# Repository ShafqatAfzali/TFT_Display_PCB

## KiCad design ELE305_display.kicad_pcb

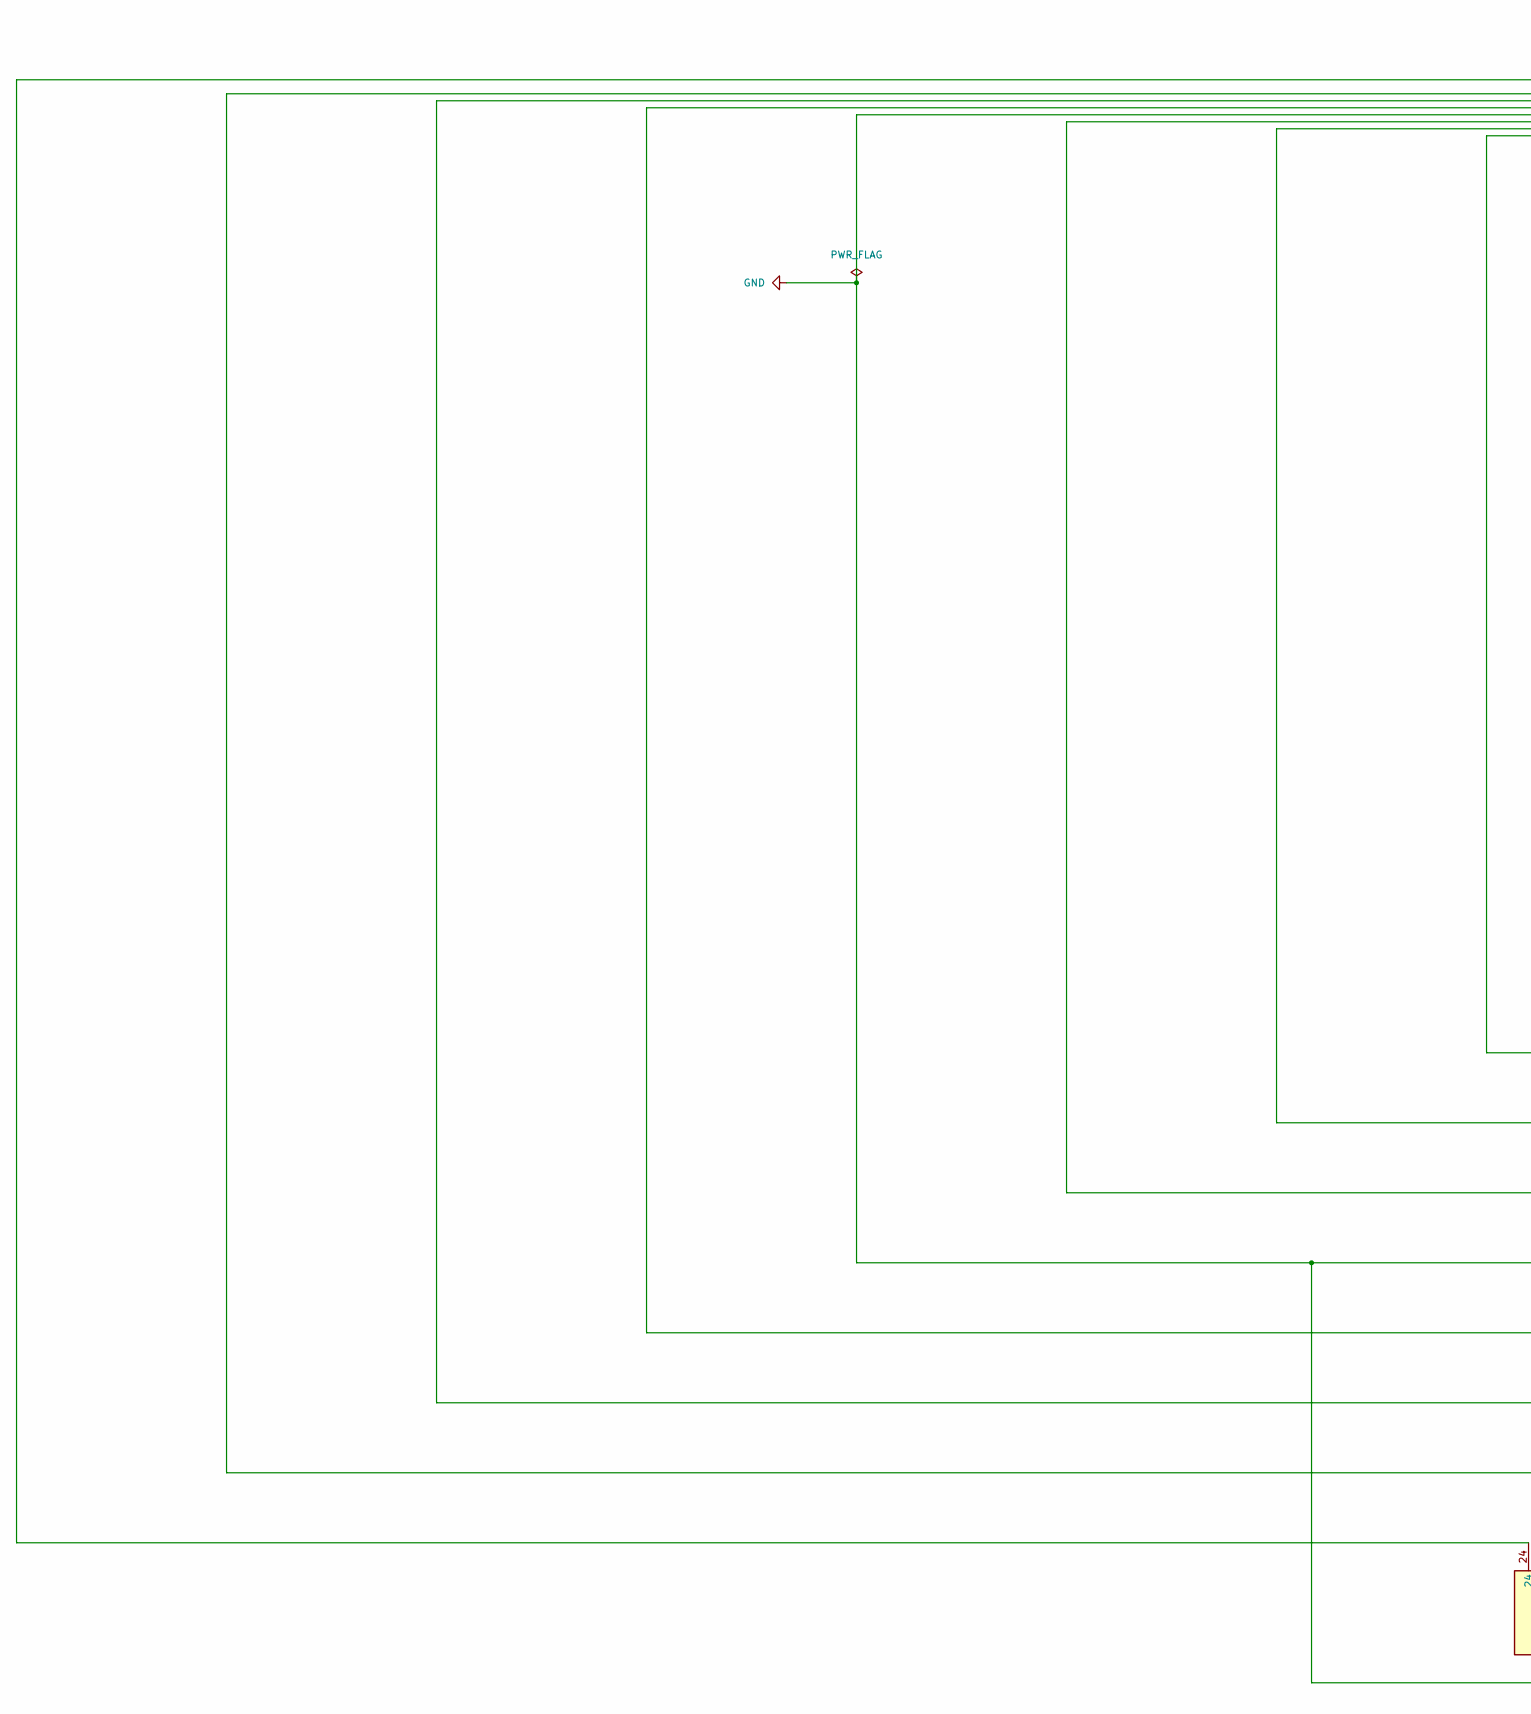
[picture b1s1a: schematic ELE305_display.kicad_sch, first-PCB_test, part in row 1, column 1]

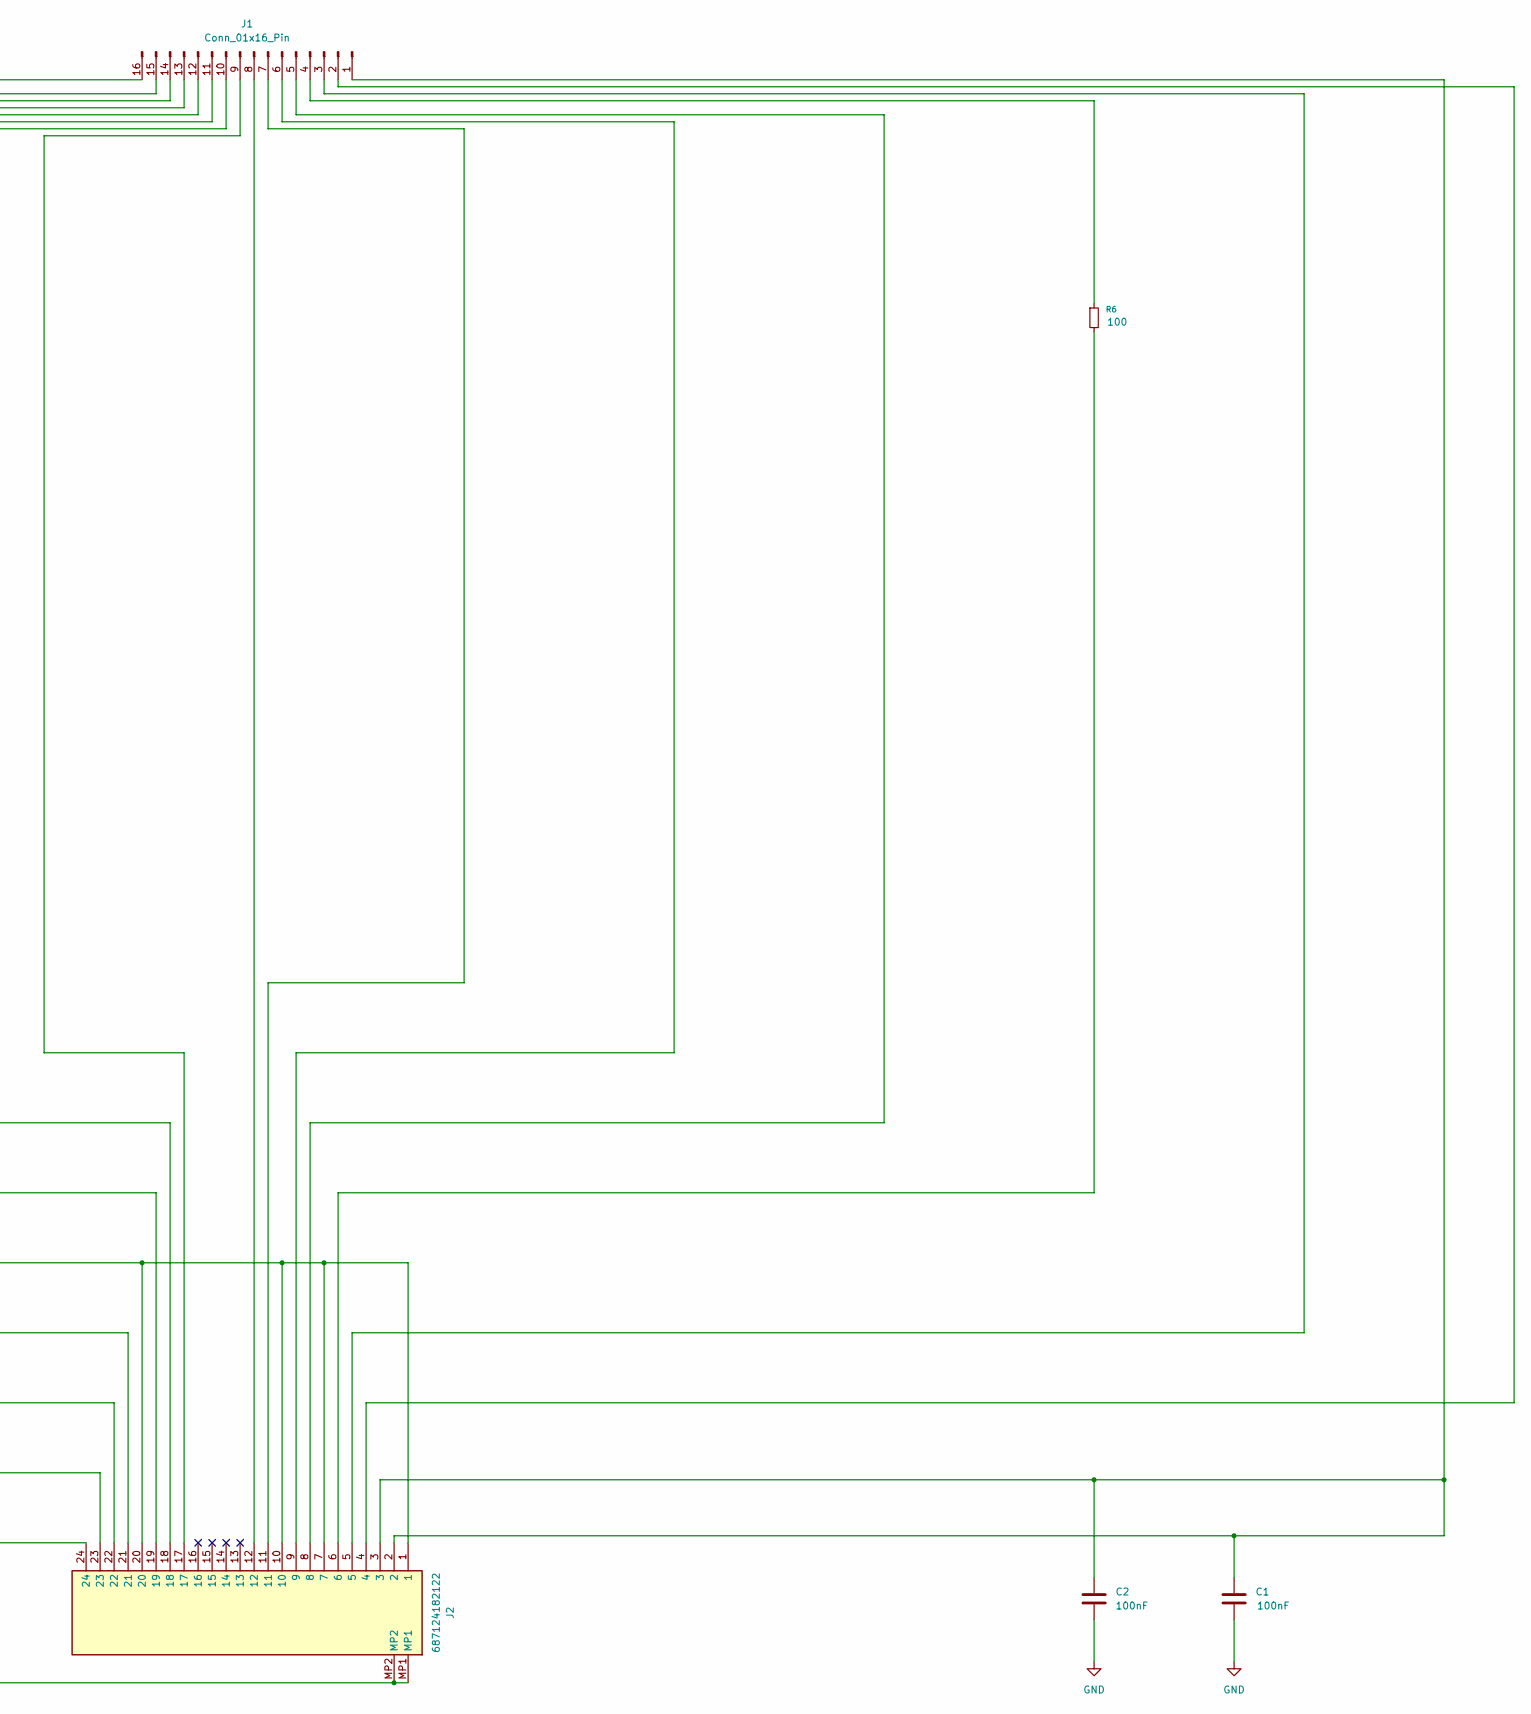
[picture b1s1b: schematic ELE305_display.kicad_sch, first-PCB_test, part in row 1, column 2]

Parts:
C1, C2: 100nF; C_Rect_L7.0mm_W2.5mm_P5.00mm
J1: Conn_01x16_Pin; PinHeader_1x16_P2.54mm_Vertical
J2: 687124182122; ELE305_connector.kicad_mod; Mouser Part Number 710-687124182122
R6: 100; R_Axial_DIN0207_L6.3mm_D2.5mm_P10.16mm_Horizontal

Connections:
GND: C1.1, C2.1, J1.12, J2.1, J2.7, J2.10, J2.20, J2.MP1, J2.MP2
unnamed: C1.2, C2.2, J1.1, J2.2, J2.3
unnamed: J1.2, J2.4
unnamed: J1.3, J2.5
unnamed: J1.4, R6.1
unnamed: J1.5, J2.8
unnamed: J1.6, J2.9
unnamed: J1.7, J2.11
unnamed: J1.8, J2.12
unnamed: J1.9, J2.17
unnamed: J1.10, J2.18
unnamed: J1.11, J2.19
unnamed: J1.13, J2.21
unnamed: J1.14, J2.22
unnamed: J1.15, J2.23
unnamed: J1.16, J2.24
unnamed: J2.6, R6.2

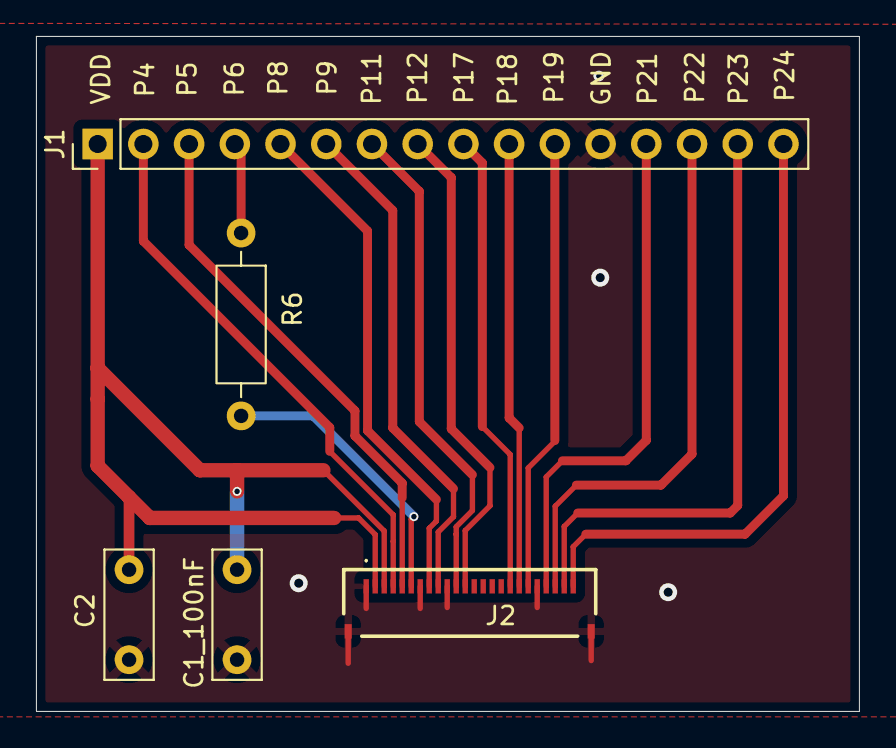
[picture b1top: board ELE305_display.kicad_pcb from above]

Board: 2 copper layers, 45.7 x 37.5 mm, 5 parts (0 on the bottom side), 17 nets.

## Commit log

2026-02-05 final pcb
2026-02-05 polished pcb
2026-02-07 Updated PCB
2026-02-09 last commit
2026-02-11 siste endring på pcb-en
